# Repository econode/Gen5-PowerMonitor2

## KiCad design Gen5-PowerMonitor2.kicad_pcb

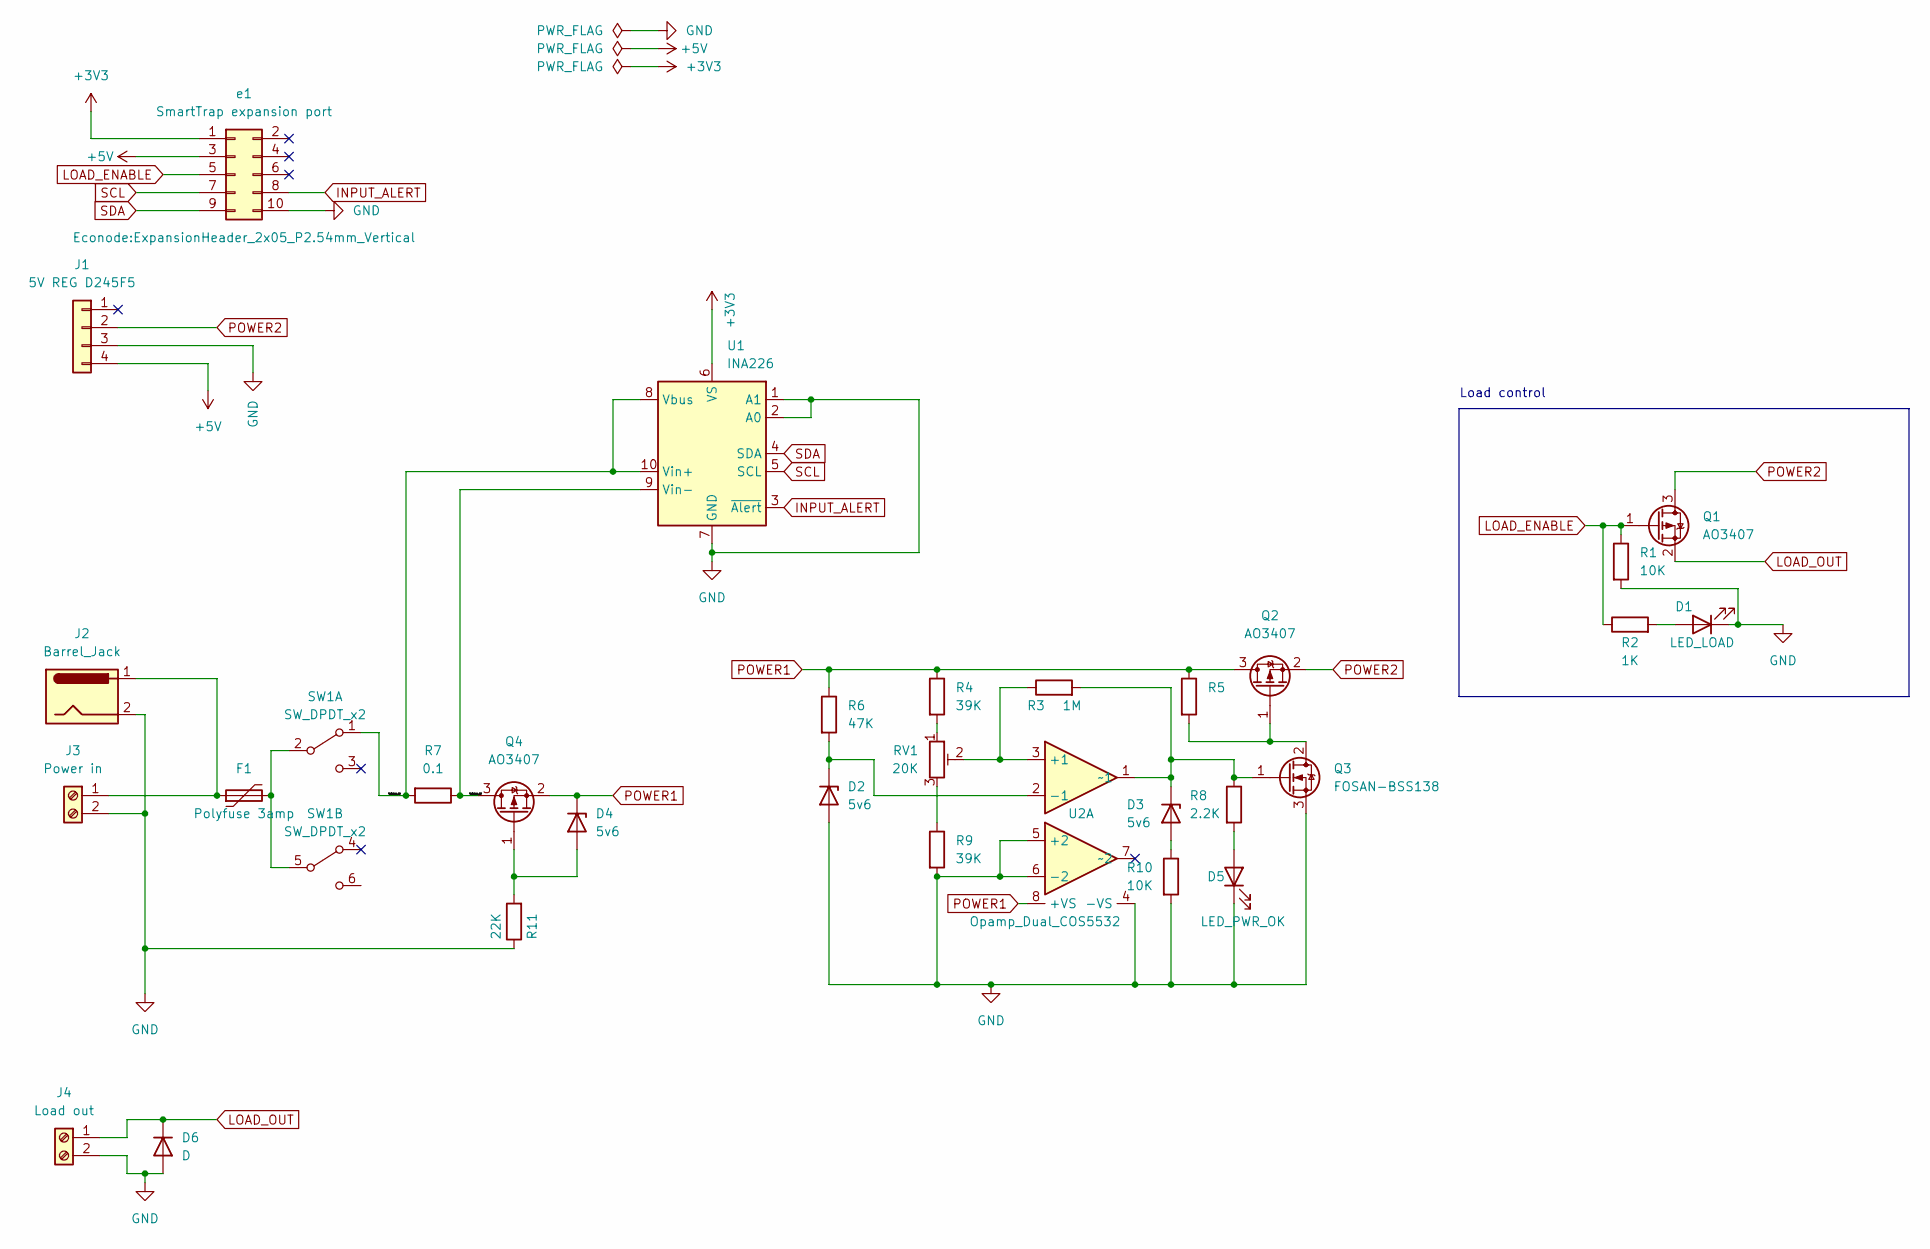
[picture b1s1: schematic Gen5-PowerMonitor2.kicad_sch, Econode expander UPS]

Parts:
D1: LED_LOAD; LED_0603_1608Metric
D2, D3, D4: 5v6; D_SOD-123
D5: LED_PWR_OK; LED_0603_1608Metric_Pad1.05x0.95mm_HandSolder
D6: D; D_0603_1608Metric_Pad1.05x0.95mm_HandSolder
F1: Polyfuse 3amp; Fuse_2920_7451Metric_Pad2.10x5.45mm_HandSolder
J1: 5V REG D245F5; PinHeader_1x04_P2.54mm_Vertical
J2: Barrel_Jack; BarrelJack_Horizontal
J3: Power in; TerminalBlock_Altech_AK300-2_P5.00mm
J4: Load out; TerminalBlock_Altech_AK300-2_P5.00mm
Q1, Q2, Q4: AO3407; SOT-23
Q3: FOSAN-BSS138; TSOT-23
R1, R10: 10K; R_0603_1608Metric
R2: 1K; R_0603_1608Metric
R3: 1M; R_0603_1608Metric
R4, R9: 39K; R_0603_1608Metric
R5: (no value)
R6: 47K; R_0603_1608Metric
R7: 0.1; R_2512_6332Metric
R8: 2.2K; R_0603_1608Metric
R11: 22K; R_0603_1608Metric
RV1: 20K; Potentiometer_Bourns_3224W_Vertical
SW1: SW_DPDT_x2; Slide-SW_DPDT_9.1mmx6.9mmP2.5
U1: INA226; VSSOP-10_3x3mm_P0.5mm
U2: Opamp_Dual_COS5532; SOP-8_3.76x4.96mm_P1.27mm
e1: SmartTrap expansion port; ExpansionHeader_2x05_P2.54mm_Vertical

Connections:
+3V3: U1.6 (VS), e1.1
+5V: J1.4, e1.3
/C_Sense_p1: R7.2, SW1.1 (A), U1.8 (Vbus), U1.10 (Vin+)
/C_Sense_p2: Q4.3 (D), R7.1, U1.9 (Vin-)
GND: D1.1 (K), D2.2 (A), D5.1 (K), D6.2 (A), J1.3, J2.2, J3.2, J4.2, Q3.3 (S), R1.2, R9.2, R10.2, R11.1, U1.1 (A1), U1.2 (A0), U1.7 (GND), U2.4 (-VS), U2.5 (+2), U2.6 (-2), e1.10
INPUT_ALERT: U1.3 (~Alert), e1.8
LOAD_ENABLE: Q1.1 (G), R1.1, R2.1, e1.5
LOAD_OUT: D6.1 (K), J4.1, Q1.2 (S)
unnamed: D1.2 (A), R2.2
unnamed: D2.1 (K), R6.2, U2.2 (-1)
unnamed: D3.1 (K), Q3.1 (G), R3.2, R8.1, U2.1 (~1)
unnamed: D3.2 (A), R10.1
unnamed: D4.2 (A), Q4.1 (G), R11.2
unnamed: D5.2 (A), R8.2
unnamed: F1.1, J2.1, J3.1
unnamed: F1.2, SW1.2 (B), SW1.5 (B)
unnamed: Q2.1 (G), Q3.2 (D), R5.2
unnamed: R4.2, RV1.1
unnamed: R9.1, RV1.3
unnamed: R3.1, RV1.2, U2.3 (+1)
POWER1: D4.1 (K), Q2.3 (D), Q4.2 (S), R4.1, R5.1, R6.1, U2.8 (+VS)
POWER2: J1.2, Q1.3 (D), Q2.2 (S)
SCL: U1.5 (SCL), e1.7
SDA: U1.4 (SDA), e1.9

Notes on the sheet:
Load control

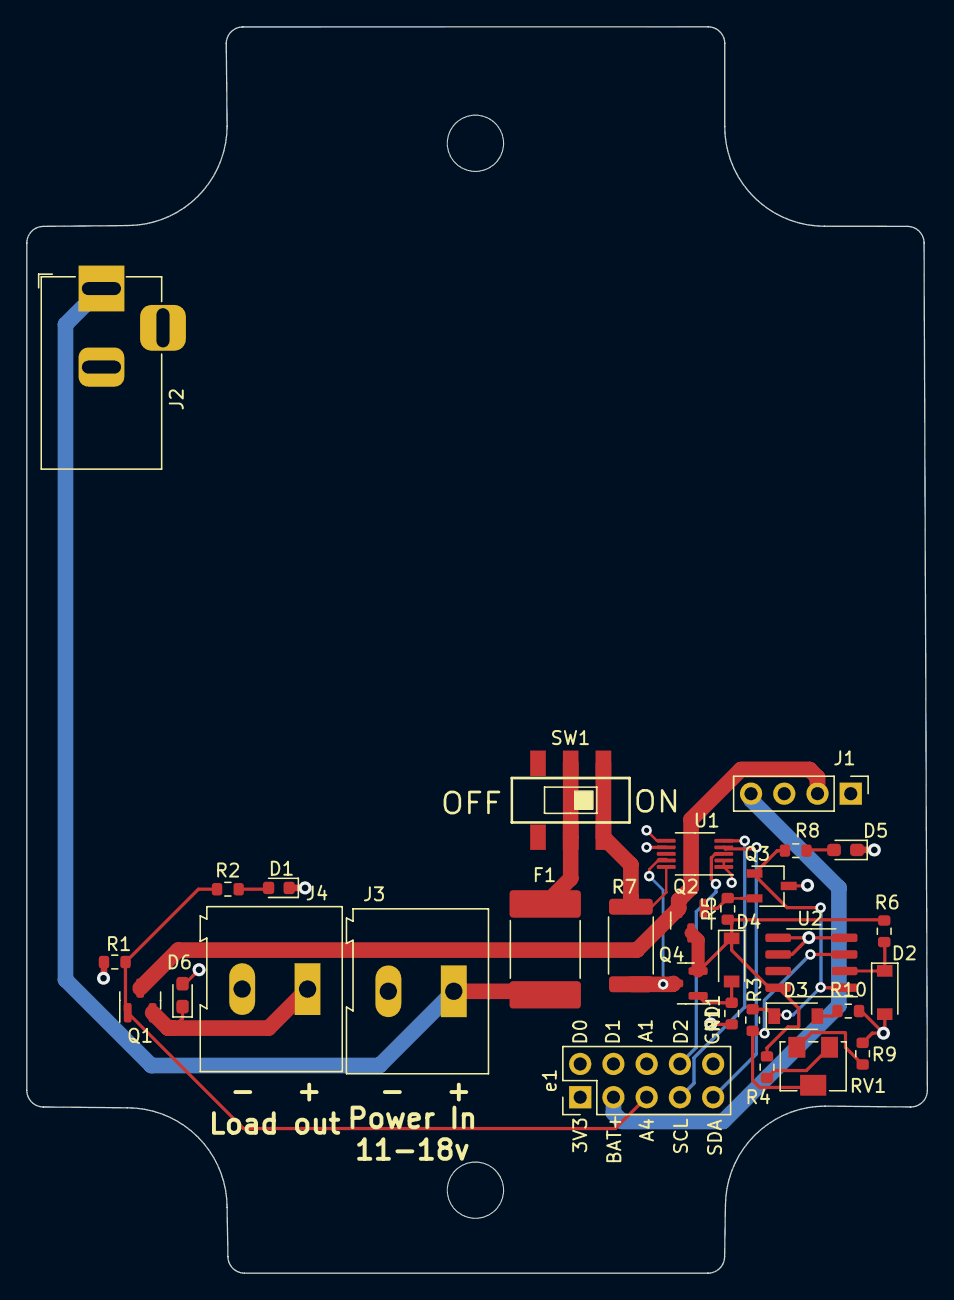
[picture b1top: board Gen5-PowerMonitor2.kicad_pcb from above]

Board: 4 copper layers, 68.8 x 95.2 mm, 31 parts (0 on the bottom side), 24 nets.
